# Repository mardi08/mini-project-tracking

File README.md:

# V3M Face Follower

>Image sources:
- http://myhealthlist.us/photo/139601/peloton-and-the-power-of-commercial-spirituality.jpg

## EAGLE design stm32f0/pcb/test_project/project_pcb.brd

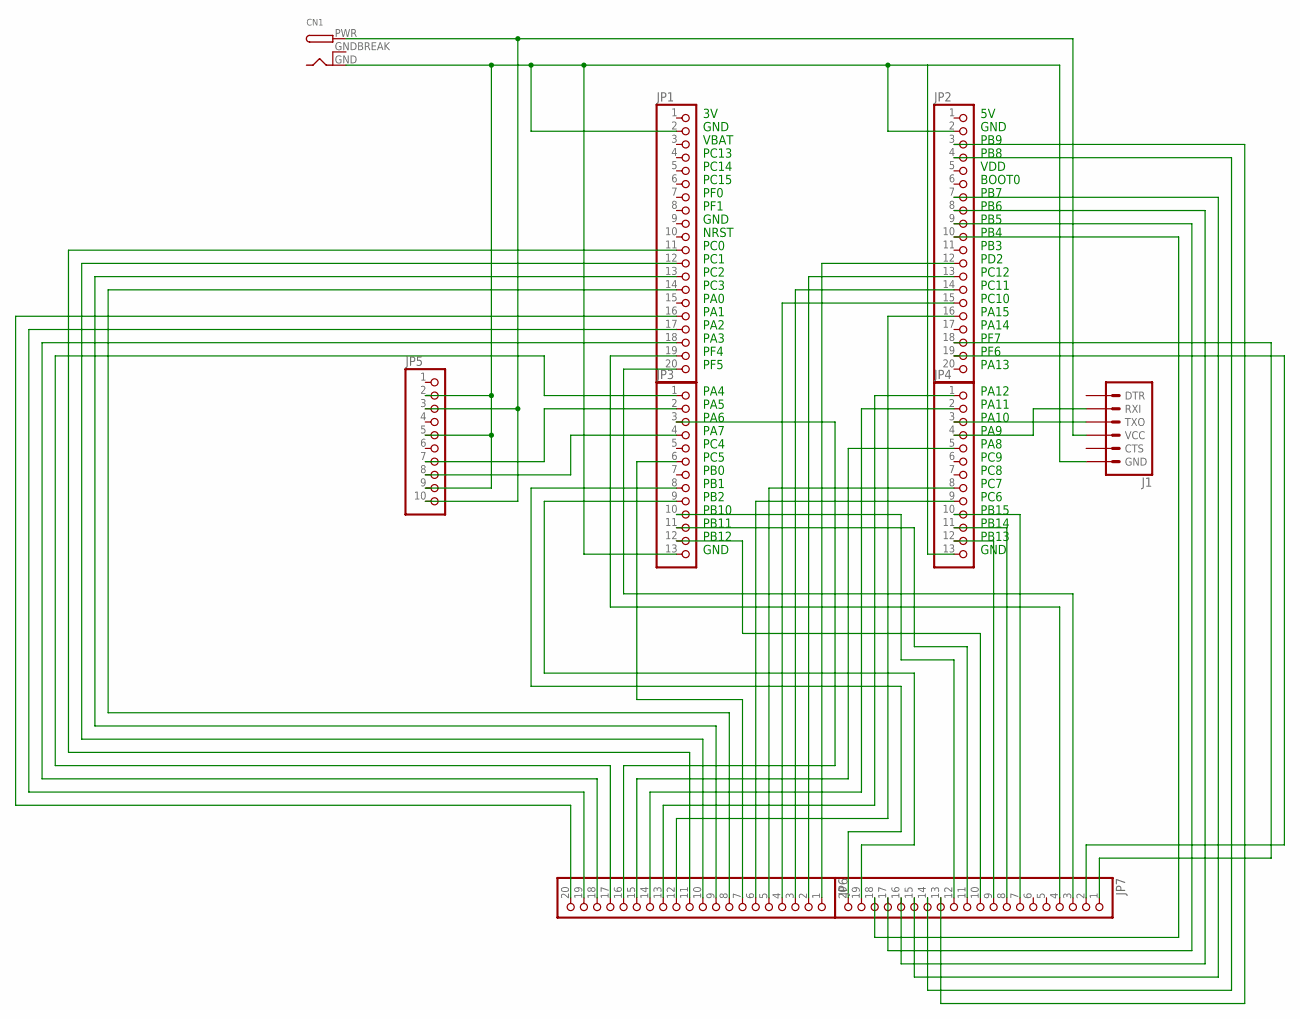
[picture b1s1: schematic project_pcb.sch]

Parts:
CN1: DCBARRELPTH; DCJACK_2MM_PTH
J1: 6_PIN_SERIAL_TARGET; 1X06
JP1, JP2, JP6, JP7: PINHD-1X20; 1X20
JP3, JP4: PINHD-1X13; 1X13
JP5: PINHD-1X10; 1X10

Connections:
GNDBREAK: CN1.GNDBREAK
unnamed: J1.3 (TXO), JP4.3
unnamed: J1.2 (RXI), JP4.4
unnamed: CN1.PWR, J1.4 (VCC), JP5.3, JP5.10
unnamed: CN1.GND, J1.6 (GND), JP1.2, JP2.2, JP3.13, JP4.13, JP5.2, JP5.5, JP5.9
unnamed: JP3.2, JP5.7
unnamed: JP3.4, JP5.8
unnamed: JP1.16, JP6.20
unnamed: JP1.17, JP6.19
unnamed: JP1.18, JP6.18
unnamed: JP3.1, JP6.17
unnamed: JP3.3, JP6.16
unnamed: JP4.5, JP6.15
unnamed: JP4.2, JP6.14
unnamed: JP4.1, JP6.13
unnamed: JP2.16, JP6.12
unnamed: JP1.11, JP6.11
unnamed: JP1.12, JP6.10
unnamed: JP1.13, JP6.9
unnamed: JP1.14, JP6.8
unnamed: JP3.6, JP6.7
unnamed: JP4.9, JP6.6
unnamed: JP4.8, JP6.5
unnamed: JP2.15, JP6.4
unnamed: JP2.14, JP6.3
unnamed: JP2.13, JP6.2
unnamed: JP2.10, JP7.18
unnamed: JP3.8, JP7.20
unnamed: JP3.9, JP7.19
unnamed: JP2.9, JP7.17
unnamed: JP2.8, JP7.16
unnamed: JP2.7, JP7.15
unnamed: JP2.4, JP7.14
unnamed: JP2.3, JP7.13
unnamed: JP3.10, JP7.12
unnamed: JP3.11, JP7.11
unnamed: JP3.12, JP7.10
unnamed: JP4.12, JP7.9
unnamed: JP4.11, JP7.8
unnamed: JP4.10, JP7.7
unnamed: JP2.18, JP7.1
unnamed: JP2.19, JP7.2
unnamed: JP1.20, JP7.3
unnamed: JP1.19, JP7.4
unnamed: JP2.12, JP6.1

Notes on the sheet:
GND
VBAT
PC13
PC14
PC15
PF0
PF1
NRST
PC0
PC1
PC2
PC3
PA0
PA1
PA2
PA3
PF4
PF5
PA4
PA5
PA6
PA7
PC4
PC5
PB0
PB1
PB2
PB10
PB11
PB12
PB9
PB8
VDD
BOOT0
PB7
PB6
PB5
PB4
PB3
PD2

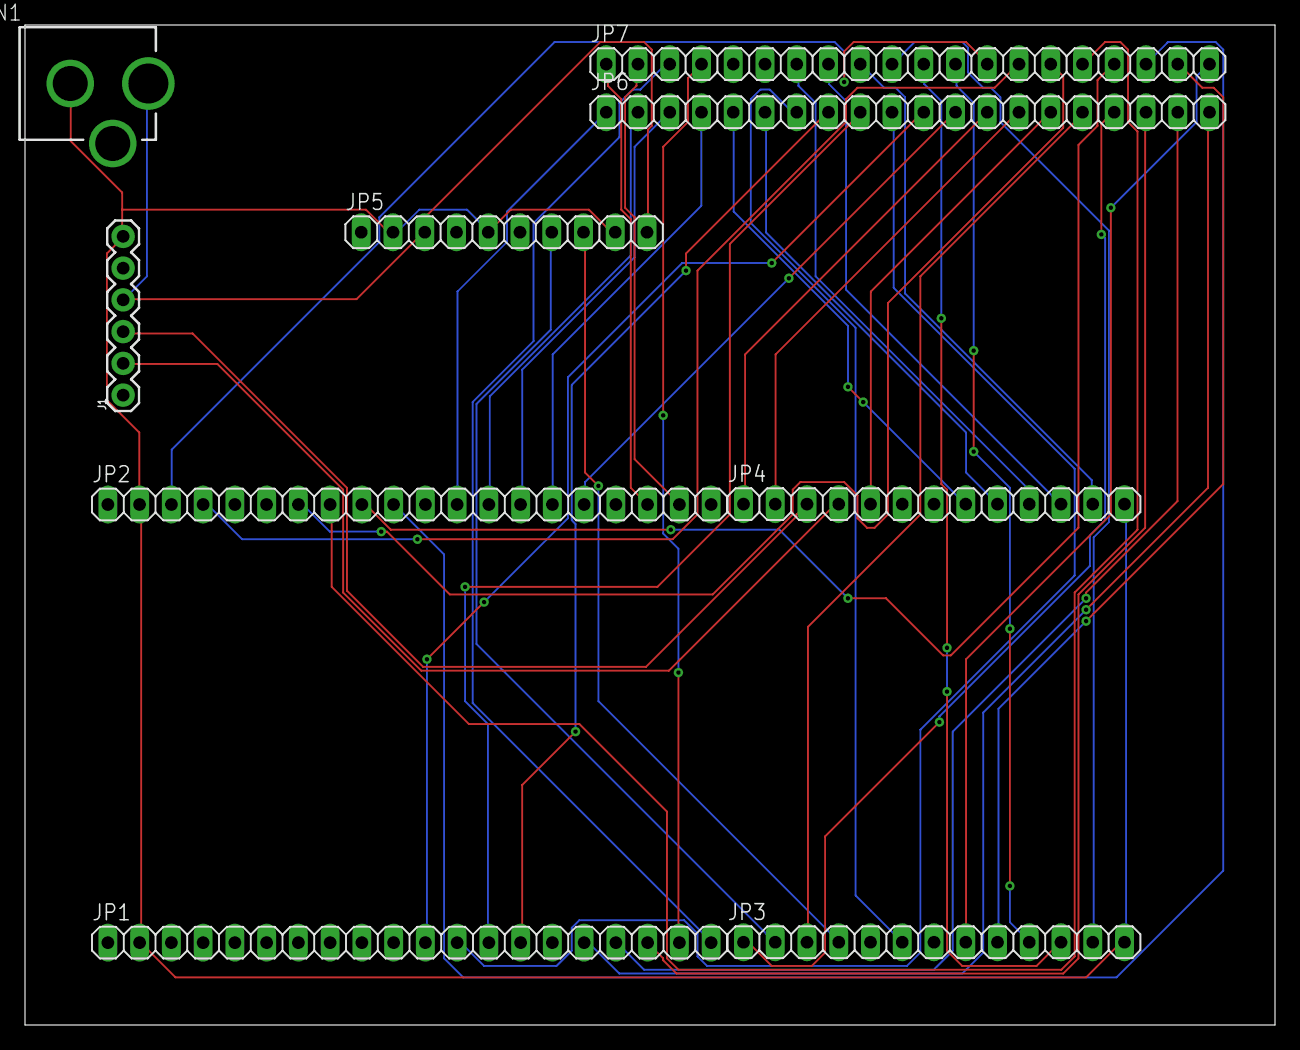
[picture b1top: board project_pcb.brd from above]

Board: 2 copper layers, 100.0 x 80.0 mm, 9 parts (0 on the bottom side), 44 nets.

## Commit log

2018-03-22 my first lalala
2018-03-23 update README.md for github guide
2018-03-23 Test code for face tracking
2018-03-24 Some changes to be able to compile with gcc
2018-03-24 Reference for compiling with gcc
2018-03-30 Add update for gcc command
2018-03-30 Addition to Title
2018-04-13 adjustment
2018-04-19 more accurate face detection and serial test
2018-04-20 updated working serial
2018-04-21 adjusted opencv code and arduino sketch for LCD
2018-04-23 LCD code update and minor opencv code changes for testing
2018-04-23 lcd i2c update
2018-04-24 Added Reset button for LCD touch and minor opencv changes
2018-04-28 final code
2018-04-28 directory with all the code for stm32f0
2018-09-27 added stm32f0 embedded code and updated readme
2018-09-27 updated readme, added poster png file
2018-09-27 fixed poster view on readme
2018-09-27 added image sources references section

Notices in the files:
parts and their libraries:
SparkFun-Connectors: Licensing: Creative Commons ShareAlike 4.0 International - https://creativecommons.org/licenses/by-sa/4.0
